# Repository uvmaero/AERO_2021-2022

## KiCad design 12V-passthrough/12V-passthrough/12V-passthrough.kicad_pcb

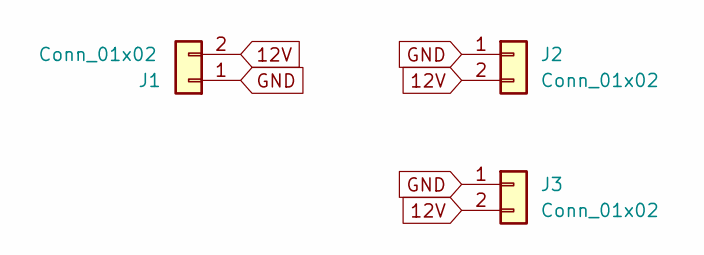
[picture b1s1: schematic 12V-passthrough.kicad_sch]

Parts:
J1, J2, J3: Conn_01x02; JST_XH_S2B-XH-A-1_1x02_P2.50mm_Horizontal

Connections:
12V: J1.2, J2.2, J3.2
GND: J1.1, J2.1, J3.1

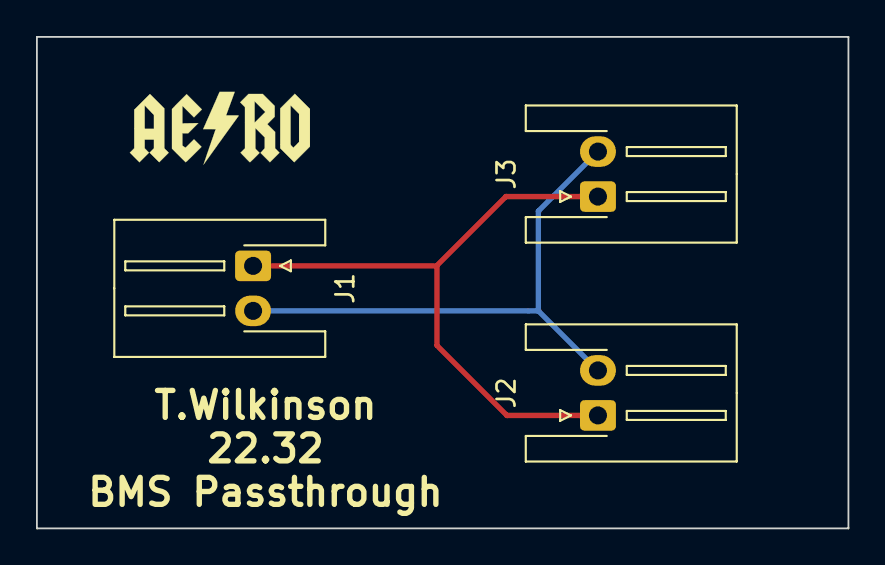
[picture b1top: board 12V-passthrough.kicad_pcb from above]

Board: 2 copper layers, 45.1 x 27.3 mm, 3 parts (0 on the bottom side), 2 nets.

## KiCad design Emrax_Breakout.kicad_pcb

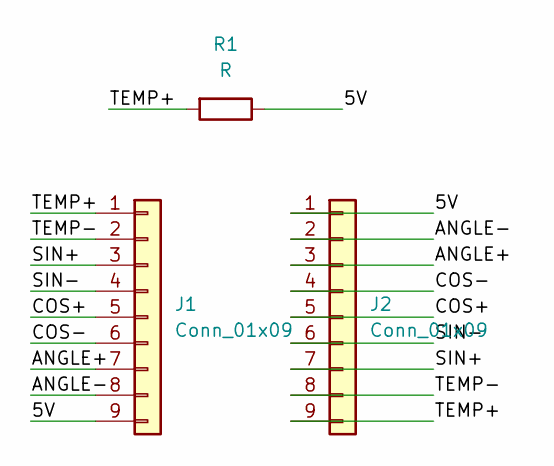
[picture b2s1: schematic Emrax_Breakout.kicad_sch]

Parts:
J1, J2: Conn_01x09; JST_XH_S9B-XH-A-1_1x09_P2.50mm_Horizontal
R1: R; R_0603_1608Metric_Pad0.98x0.95mm_HandSolder

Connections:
/5V: J1.9, J2.1, R1.1
/ANGLE+: J1.7, J2.3
/ANGLE-: J1.8, J2.2
/COS+: J1.5, J2.5
/COS-: J1.6, J2.4
/SIN+: J1.3, J2.7
/SIN-: J1.4, J2.6
/TEMP+: J1.1, J2.9, R1.2
/TEMP-: J1.2, J2.8

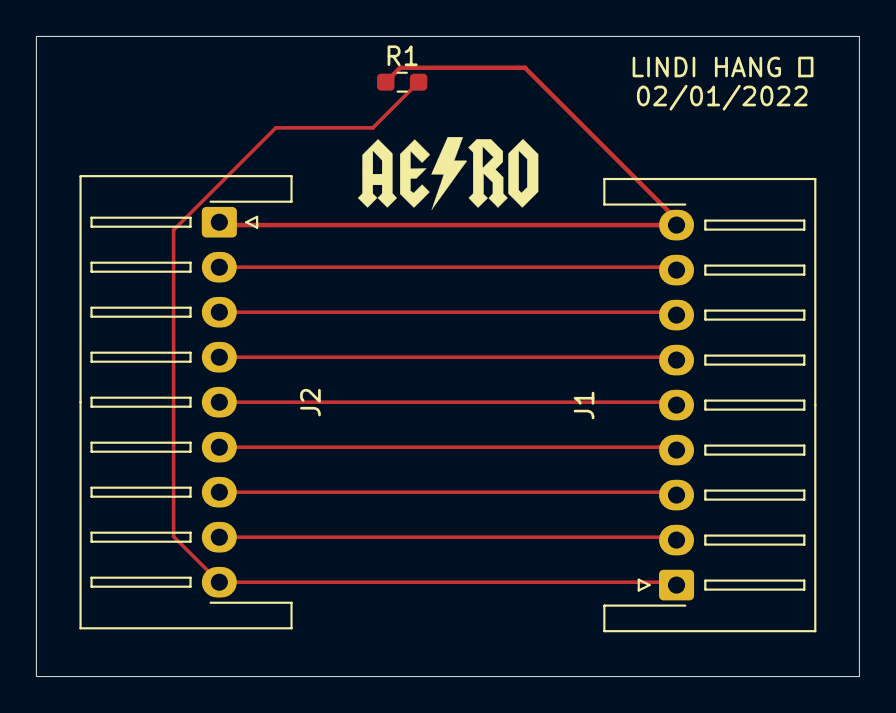
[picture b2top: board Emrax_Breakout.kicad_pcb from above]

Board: 2 copper layers, 45.7 x 35.6 mm, 3 parts (0 on the bottom side), 9 nets.
